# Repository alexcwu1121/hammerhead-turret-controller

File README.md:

# hammerhead-turret-controller

To build:
1. Install Podman >4.x
2. Install VSCode
3. Install VSCode Dev Containers extension
4. In Dev Containers settings, set the following:
    - Docker Path: `podman`
    - Docker Compose Path: `podman-compose`
    - Docker Socket: `/run/podman/podman.sock`

To quick-run pre-commit, builds, tests:
`podman-compose run --build pre-commit`
`podman-compose run --build build-debug`
`podman-compose run --build build-release`

CAN ID claims:
- Pub: 0x300 - 0x3FF
- Sub: 0x400 - 0x4FF

`arm-none-eabi-objcopy -O binary htc.elf htc.bin`

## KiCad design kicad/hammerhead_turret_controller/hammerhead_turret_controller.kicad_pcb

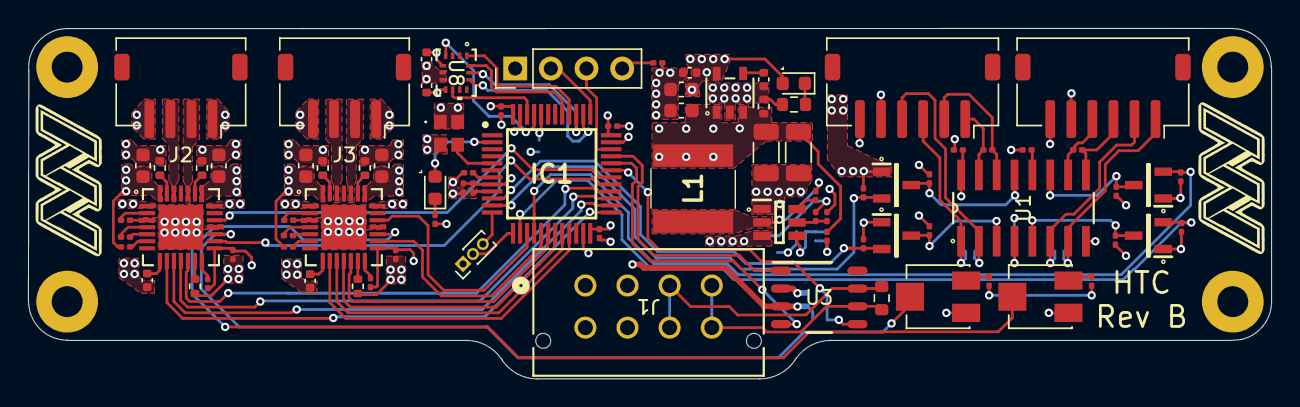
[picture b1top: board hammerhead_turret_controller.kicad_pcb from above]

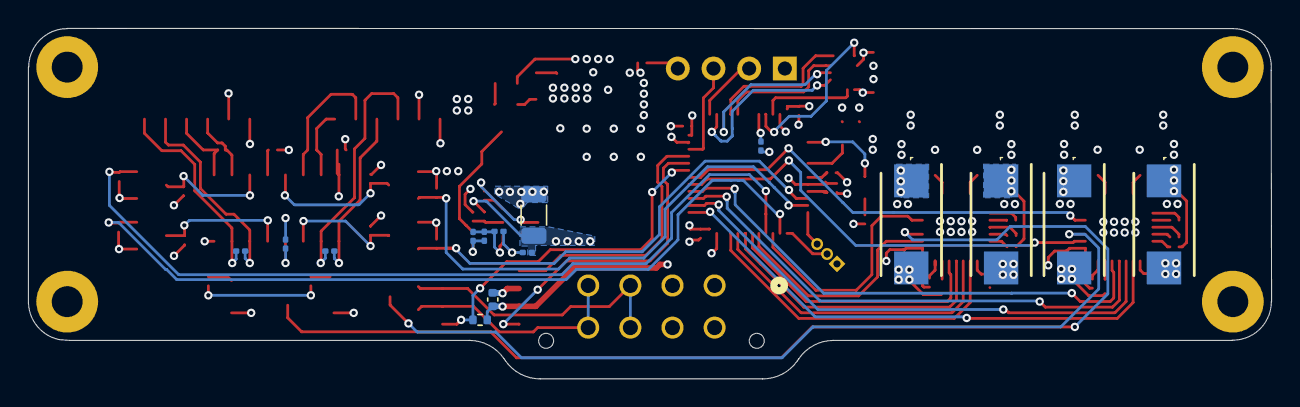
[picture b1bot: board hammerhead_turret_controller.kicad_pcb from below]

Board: 4 copper layers, 88.5 x 25.0 mm, 99 parts (15 on the bottom side), 91 nets.

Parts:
C1: 10uF; C_1206_3216Metric
C2, C4, C7, C30, C31, C32, C33, C34, C42, C43, C52, C53: 0.1uF; C_0201_0603Metric
C3, C49: 0.22uF; C_0201_0603Metric
C6: 1uF; C_0603_1608Metric
C8: 22nF; C_0402_1005Metric
C9, C12: 22uF; C_1206_3216Metric
C10, C11, C15, C19: 0.1uF; C_0402_1005Metric
C13: 10uF; C_0603_1608Metric
C14: 75pF; C_0201_0603Metric
C29, C51: 0.22uF; C_0402_1005Metric
C35: 1uF; C_0201_0603Metric
C44, C45, C54, C55: 293D107X9016D2TE3; CAPPM7343X310N
C47, C48, C57, C58: 0.1uF; C_0603_1608Metric
D2: LED, 0603, RED; D_0603_1608Metric
D3: LED, 0603, BLUE; D_0603_1608Metric
IC1: STM32F302CBT6; QFP50P900X900X160-48N
J1: 430450812; CONN_SD-43045-005_08_MOL
J2, J3: B4B-XH-A; JST_ZH_S4B-ZR-SM4A-TF_1x04-1MP_P1.50mm_Horizontal
J4, J5: B6B-XH-A_LF__SN_; JST_ZH_S6B-ZR-SM4A-TF_1x06-1MP_P1.50mm_Horizontal
J6: Conn_01x03; PinHeader_1x03_P1.00mm_Vertical
J8: SWD; PinHeader_1x04_P2.54mm_Vertical
L1: NR6028T150M
PS1: TPS54202DDCR; SOT95P280X110-6N
Q1, Q2, Q3, Q4: BSS138LT1G; SOT96P237X111-3N
R1: 511k; R_0201_0603Metric
R2: 105k; R_0201_0603Metric
R3, R4: 5k; R_0201_0603Metric
R5, R8, R10, R12, R13, R14, R15, R16, R17, R18, R30, R31: 10k; R_0201_0603Metric
R6, R7, R9, R11: 120; R_0201_0603Metric
R19, R26: 22k; R_0201_0603Metric
R20, R24, R46, R58: 10k; R_0402_1005Metric
R21: 49.9k; R_0201_0603Metric
R22, R40, R52: 100k; R_0201_0603Metric
R23: 13.3k; R_0201_0603Metric
R25: 120; R_0603_1608Metric
R29: 1k; R_0201_0603Metric
R32: 1k; R_0603_1608Metric
R47, R48, R59, R60: 0.22; R_0402_1005Metric
U1: MC3486DR; D16
U2: RT9193-33GB; SOT-23-5_RIT
U3: TCAN337DR; D0008A_N
U8: BMI270; BMI270_BOS
U10, U13: A4988SETTR-T; QFN-28_ALM
VR3, VR4: 3314J-1-103E; TRIM_3314J-1-103E
Y1: ASDDV-24.000MHZ-LC-T; AbraconASDDV

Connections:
3V3: C3.2, C10.1, C11.2, C13.2, C15.1, C19.2, C30.1, C31.1, C32.1, C33.1, C34.1, C35.1, C49.2, D3.2 (A), IC1.9 (VDDA), IC1.24 (VDD_1), IC1.36 (VDD_2), IC1.48 (VDD_3), J8.4, Q1.1 (G), Q2.1 (G), Q3.1 (G), Q4.1 (G), R3.2, R4.2, R10.1, R13.1, R15.1, R16.1, R19.1, R24.1, R26.1, R30.1, U2.5 (VOUT), U3.3 (VCC), U8.5 (VDDIO), U8.8 (VDD), U10.15 (VDD), U13.15 (VDD), Y1.1 (TRI-STATE), Y1.4 (VDD)
5V: C4.2, C6.2, C9.1, C12.1, J4.6, J5.6, L1.2, R5.1, R8.2, R12.1, R14.1, R17.1, R18.1, R20.1, R21.1, U1.16 (VCC), U2.1 (VIN), U2.3 (EN)
14.8V: C1.1, C2.1, C43.2, C44.1 (+), C45.1 (+), C47.1, C48.1, C53.2, C54.1 (+), C55.1 (+), C57.1, C58.1, J1.1, J1.5, PS1.3 (VIN), R1.2, U10.22 (VBB1), U10.28 (VBB2), U13.22 (VBB1), U13.28 (VBB2)
/CANH: J1.3, J1.7, R25.1, U3.7 (CANH)
/CANL: J1.4, J1.8, R25.2, U3.6 (CANL)
/CAN_FAULT: IC1.31 (PA10), R24.2, U3.5 (FAULT)
/CAN_RX: IC1.32 (PA11), U3.4 (RXD)
/CAN_TX: IC1.33 (PA12), U3.1 (TXD)
/Encoders/PAN_EA_5V: Q1.3 (D), R12.2, U1.3 (1Y)
/Encoders/PAN_EB_5V: Q3.3 (D), R17.2, U1.13 (4Y)
/Encoders/TILT_EA_5V: Q4.3 (D), R18.2, U1.11 (3Y)
/Encoders/TILT_EB_5V: Q2.3 (D), R14.2, U1.5 (2Y)
/MCU/BOOT0: IC1.44 (BOOT0), R31.2
/MCU/FAULT_LED: D2.2 (A), IC1.2 (PC13)
/MCU/IMU_IT_1: IC1.45 (PB8), U8.4 (INT1)
/MCU/IMU_IT_2: IC1.46 (PB9), U8.9 (INT2)
/MCU/NRST: IC1.7 (NRST), R30.2
/MCU/OSC_IN: IC1.5 (PF0/OSC_IN), Y1.3 (OUTPUT)
/MCU/PAN_DIR: IC1.30 (PA9), U10.19 (DIR)
/MCU/PAN_ENC_A: IC1.10 (PA0), Q1.2 (S), R10.2
/MCU/PAN_ENC_B: IC1.11 (PA1), Q3.2 (S), R15.2
/MCU/PAN_MS1: IC1.25 (PB12), U10.9 (MS1)
/MCU/PAN_MS2: IC1.26 (PB13), U10.10 (MS2)
/MCU/PAN_MS3: IC1.27 (PB14), U10.11 (MS3)
/MCU/PAN_RESET: IC1.28 (PB15), U10.12 (*RESET)
/MCU/PAN_STEP: IC1.29 (PA8), U10.16 (STEP)
/MCU/SPI_MISO: IC1.40 (PB4), U8.1 (SDO)
/MCU/SPI_MOSI: IC1.41 (PB5), U8.14 (SDX)
/MCU/SPI_SCK: IC1.39 (PB3), U8.13 (SCX)
/MCU/SWCLK: IC1.37 (PA14), J8.2
/MCU/SWDIO: IC1.34 (PA13), J8.3
/MCU/TC_SPI_CS: IC1.38 (PA15), U8.12 (CSB)
/MCU/TILT_DIR: IC1.15 (PA5), U13.19 (DIR)
/MCU/TILT_ENC_A: IC1.16 (PA6), Q4.2 (S), R16.2
/MCU/TILT_ENC_B: IC1.14 (PA4), Q2.2 (S), R13.2
/MCU/TILT_MS1: IC1.21 (PB10), U13.9 (MS1)
/MCU/TILT_MS2: IC1.20 (PB2), U13.10 (MS2)
/MCU/TILT_MS3: IC1.19 (PB1), U13.11 (MS3)
/MCU/TILT_RESET: IC1.18 (PB0), U13.12 (*RESET)
/MCU/TILT_STEP: IC1.17 (PA7), U13.16 (STEP)
/MCU/UART_RX: IC1.13 (PA3), J6.2
/MCU/UART_TX: IC1.12 (PA2), J6.3
/PAN_EA_HI: J4.4, R6.2, U1.2 (1A)
/PAN_EA_LO: J4.3, R6.1, U1.1 (1B)
/PAN_EB_HI: J4.2, R9.2, U1.14 (4A)
/PAN_EB_LO: J4.1, R9.1, U1.15 (4B)
/PAN_OUT1A: J2.2, U10.24 (OUT1A)
/PAN_OUT1B: J2.1, U10.21 (OUT1B)
/PAN_OUT2A: J2.3, U10.26 (OUT2A)
/PAN_OUT2B: J2.4, U10.1 (OUT2B)
/TILT_EA_HI: J5.4, R11.1, U1.10 (3A)
/TILT_EA_LO: J5.3, R11.2, U1.9 (3B)
/TILT_EB_HI: J5.2, R7.1, U1.6 (2A)
/TILT_EB_LO: J5.1, R7.2, U1.7 (2B)
/TILT_OUT1A: J3.2, U13.24 (OUT1A)
/TILT_OUT1B: J3.1, U13.21 (OUT1B)
/TILT_OUT2A: J3.3, U13.26 (OUT2A)
/TILT_OUT2B: J3.4, U13.1 (OUT2B)
GND: C1.2, C2.2, C3.1, C4.1, C6.1, C8.1, C9.2, C10.2, C11.1, C12.2, C13.1, C15.2, C19.1, C29.2, C30.2, C31.2, C32.2, C33.2, C34.2, C35.2, C44.2 (-), C45.2 (-), C47.2, C48.2, C49.1, C51.2, C54.2 (-), C55.2 (-), C57.2, C58.2, IC1.8 (VSSA/VREF-), IC1.23 (VSS_1), IC1.35 (VSS_2), IC1.47 (VSS_3), J1.2, J1.6, J4.5, J5.5, J6.1, J8.1, PS1.1 (GND), R2.1, R20.2, R23.2, R29.1, R31.1, R32.2, R40.2, R46.1, R47.2, R48.2, R52.2, R58.1, R59.2, R60.2, U1.8 (GND), U2.2 (GND), U3.2 (GND), U8.6 (GNDIO), U8.7 (GND), U10.3 (GND), U10.18 (GND), U10.29, U13.3 (GND), U13.18 (GND), U13.29, VR3.3, VR4.3, Y1.2 (GND)
unnamed: C14.1, R21.2, R22.1
unnamed: D2.1 (K), R29.2
unnamed: D3.1 (K), R32.1
unnamed: C7.1, PS1.6 (BOOT)
unnamed: PS1.5 (EN), R1.1, R2.2
unnamed: C14.2, PS1.4 (FB), R22.2, R23.1
unnamed: C7.2, L1.1, PS1.2 (SW)
unnamed: R19.2, VR3.1
unnamed: R26.2, VR4.1
unnamed: R5.2, U1.4 (1)
unnamed: R8.1, U1.12 (3)
unnamed: C8.2, U2.4 (BP)
unnamed: R40.1, U10.2 (*ENABLE)
unnamed: R3.1, U10.14 (*SLEEP)
unnamed: C42.1, U10.4 (CP1)
unnamed: C42.2, U10.5 (CP2)
unnamed: U10.17 (REF), VR3.2
unnamed: R46.2, U10.13 (ROSC)
unnamed: R48.1, U10.23 (SENSE1)
unnamed: R47.1, U10.27 (SENSE2)
unnamed: C43.1, U10.6 (VCP)
unnamed: C29.1, U10.8 (VREG)
unnamed: R52.1, U13.2 (*ENABLE)
unnamed: R4.1, U13.14 (*SLEEP)
unnamed: C52.1, U13.4 (CP1)
unnamed: C52.2, U13.5 (CP2)
unnamed: U13.17 (REF), VR4.2
unnamed: R58.2, U13.13 (ROSC)
unnamed: R60.1, U13.23 (SENSE1)
unnamed: R59.1, U13.27 (SENSE2)
unnamed: C53.1, U13.6 (VCP)
unnamed: C51.1, U13.8 (VREG)

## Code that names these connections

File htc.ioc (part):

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Mcu.Name=STM32F302C(B-C)Tx
Mcu.Package=LQFP48
Mcu.UserName=STM32F302CBTx
PA0.GPIOParameters=GPIO_Label
PA0.GPIO_Label=PAN_ENC_A
PA0.Signal=S_TIM2_CH1_ETR
PA1.GPIOParameters=GPIO_Label
PA1.GPIO_Label=PAN_ENC_B
PA1.Signal=S_TIM2_CH2
PA10.GPIOParameters=GPIO_Label
PA10.GPIO_Label=CAN_FAULT
PA10.Signal=GPIO_Input
PA11.Mode=CAN_Activate
PA11.Signal=CAN_RX
PA12.Mode=CAN_Activate
PA12.Signal=CAN_TX
PA13.Mode=Serial_Wire
PA13.Signal=SYS_JTMS-SWDIO
PA14.Mode=Serial_Wire
PA14.Signal=SYS_JTCK-SWCLK
PA15.GPIOParameters=GPIO_Label
PA15.GPIO_Label=SPI_CS
PA15.Signal=GPIO_Output
PA2.GPIOParameters=GPIO_Label
PA2.GPIO_Label=UART_TX
PA2.Mode=Asynchronous
PA2.Signal=USART2_TX
PA3.GPIOParameters=GPIO_Label
PA3.GPIO_Label=UART_RX
PA3.Mode=Asynchronous
PA3.Signal=USART2_RX
PA4.GPIOParameters=GPIO_Label
PA4.GPIO_Label=TILT_ENC_B
PA4.Signal=S_TIM3_CH2
PA5.GPIOParameters=GPIO_Label
PA5.GPIO_Label=TILT_DIR
PA5.Signal=GPIO_Output
PA6.GPIOParameters=GPIO_Label
PA6.GPIO_Label=TILT_ENC_A
PA6.Signal=S_TIM3_CH1
PA7.GPIOParameters=GPIO_Label
PA7.GPIO_Label=TILT_STEP
PA7.Signal=S_TIM17_CH1
PA8.GPIOParameters=GPIO_Label
PA8.GPIO_Label=PAN_STEP
PA8.Signal=S_TIM1_CH1
PA9.GPIOParameters=GPIO_Label
PA9.GPIO_Label=PAN_DIR
PA9.Signal=GPIO_Output
PB0.GPIOParameters=GPIO_Label
PB0.GPIO_Label=TILT_RESET
PB0.Signal=GPIO_Output
PB1.GPIOParameters=GPIO_Label
PB1.GPIO_Label=TILT_MS3
PB1.Signal=GPIO_Output
PB10.GPIOParameters=GPIO_Label
PB10.GPIO_Label=TILT_MS1
PB10.Signal=GPIO_Output
PB12.GPIOParameters=GPIO_Label
PB12.GPIO_Label=PAN_MS1
PB12.Signal=GPIO_Output
PB13.GPIOParameters=GPIO_Label
PB13.GPIO_Label=PAN_MS2
PB13.Signal=GPIO_Output
PB14.GPIOParameters=GPIO_Label
PB14.GPIO_Label=PAN_MS3
PB14.Signal=GPIO_Output
PB15.GPIOParameters=GPIO_Label
PB15.GPIO_Label=PAN_RESET
PB15.Signal=GPIO_Output
PB2.GPIOParameters=GPIO_Label
PB2.GPIO_Label=TILT_MS2
PB2.Signal=GPIO_Output
PB3.GPIOParameters=GPIO_Label
PB3.GPIO_Label=SPI_SCK
PB3.Mode=Full_Duplex_Master
PB3.Signal=SPI3_SCK
PB4.GPIOParameters=GPIO_Label
PB4.GPIO_Label=SPI_MISO
PB4.Mode=Full_Duplex_Master
PB4.Signal=SPI3_MISO
PB5.GPIOParameters=GPIO_Label
PB5.GPIO_Label=SPI_MOSI
PB5.Mode=Full_Duplex_Master
PB5.Signal=SPI3_MOSI
PB6.GPIOParameters=GPIO_Label
PB6.GPIO_Label=I2C_SCL
PB6.Mode=I2C
PB6.Signal=I2C1_SCL
PB7.GPIOParameters=GPIO_Label
PB7.GPIO_Label=I2C_SDA
PB7.Mode=I2C
PB7.Signal=I2C1_SDA
PB8.GPIOParameters=GPIO_Label
PB8.GPIO_Label=IMU_IT_1
PB8.Signal=GPIO_Input
PB9.GPIOParameters=GPIO_Label
PB9.GPIO_Label=IMU_IT_2
PB9.Signal=GPIO_Input
PC13.GPIOParameters=GPIO_Label
PC13.GPIO_Label=FAULT_LED
PC13.Signal=GPIO_Output
PF0-OSC_IN.Mode=HSE-External-Clock-Source
PF0-OSC_IN.Signal=RCC_OSC_IN
RCC.HSEPLLFreq_Value=24000000
RCC.HSE_VALUE=24000000
RCC.SYSCLKFreq_VALUE=48000000
RCC.SYSCLKSourceVirtual=RCC_SYSCLKSOURCE_PLLCLK
board=custom

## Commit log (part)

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2026-02-25 add kicad design files
2026-03-06 project generation and initial commit
